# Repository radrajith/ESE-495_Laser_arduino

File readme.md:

#creating a webpage for laser project

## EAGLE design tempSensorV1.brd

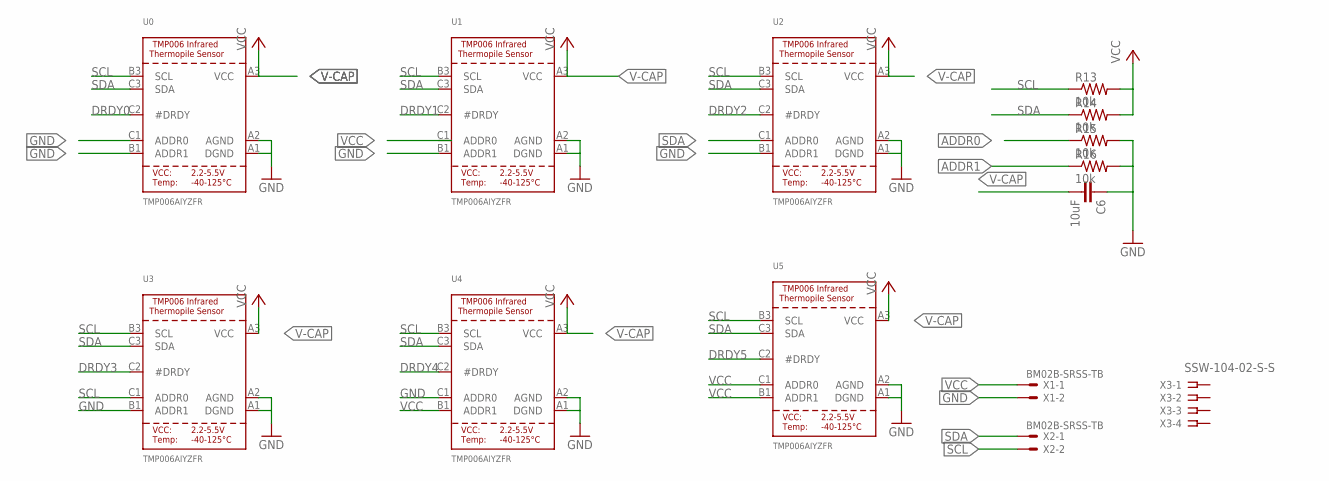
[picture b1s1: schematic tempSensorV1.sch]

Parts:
C6: 10uF; 0603-CAP
R13, R14, R15, R16: 10k; 0402-RES
U0, U1, U2, U3, U4, U5: TMP006AIYZFR; WCSP-8
X1, X2: BM02B-SRSS-TB
X3: SSW-104-02-S-S

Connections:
ADDR0: R15.1
ADDR1: R16.1
DRDY0: U0.C2 (#DRDY)
DRDY1: U1.C2 (#DRDY)
DRDY2: U2.C2 (#DRDY)
DRDY3: U3.C2 (#DRDY)
DRDY4: U4.C2 (#DRDY)
DRDY5: U5.C2 (#DRDY)
GND: C6.1, R15.2, R16.2, U0.A1 (DGND), U0.A2 (AGND), U0.B1 (ADDR1), U0.C1 (ADDR0), U1.A1 (DGND), U1.A2 (AGND), U1.B1 (ADDR1), U2.A1 (DGND), U2.A2 (AGND), U2.B1 (ADDR1), U3.A1 (DGND), U3.A2 (AGND), U3.B1 (ADDR1), U4.A1 (DGND), U4.A2 (AGND), U4.C1 (ADDR0), U5.A1 (DGND), U5.A2 (AGND), X1.2
SCL: R13.1, U0.B3 (SCL), U1.B3 (SCL), U2.B3 (SCL), U3.B3 (SCL), U3.C1 (ADDR0), U4.B3 (SCL), U5.B3 (SCL), X2.2
SDA: R14.1, U0.C3 (SDA), U1.C3 (SDA), U2.C1 (ADDR0), U2.C3 (SDA), U3.C3 (SDA), U4.C3 (SDA), U5.C3 (SDA), X2.1
V-CAP: C6.2, R13.2, R14.2, U0.A3 (VCC), U1.A3 (VCC), U2.A3 (VCC), U3.A3 (VCC), U4.A3 (VCC), U5.A3 (VCC)
VCC: U4.B1 (ADDR1), U5.B1 (ADDR1), U5.C1 (ADDR0), X1.1

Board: 2 copper layers, 14 parts (7 on the bottom side), 5 nets, no tracks yet.

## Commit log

2016-09-04 :lollipop: Added .gitattributes & .gitignore files
2016-09-04 uploading all the files used for reserach
    ESE 495 research project - laser to treat skin lesions.
2016-09-06 adding files
2016-10-13 pspice test-still not completed
2016-11-06 took data and added some files and pic
2016-11-20 created sqwave library and changed arduino code to include that and test it
2017-01-14 in the process of writing/modifying research paper
2017-01-18 Set theme jekyll-theme-architect
2017-02-03 update matlab code

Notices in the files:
parts and their libraries:
microbuilder: This work is placed in the public domain, and may be freely used for commercial and non-commercial work with the following conditions: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
SparkFun-Capacitors: Licensing: Creative Commons ShareAlike 4.0 International - https://creativecommons.org/licenses/by-sa/4.0
